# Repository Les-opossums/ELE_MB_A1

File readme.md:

# Motherboard

Electronic board - Motherboard - Main robot - A1

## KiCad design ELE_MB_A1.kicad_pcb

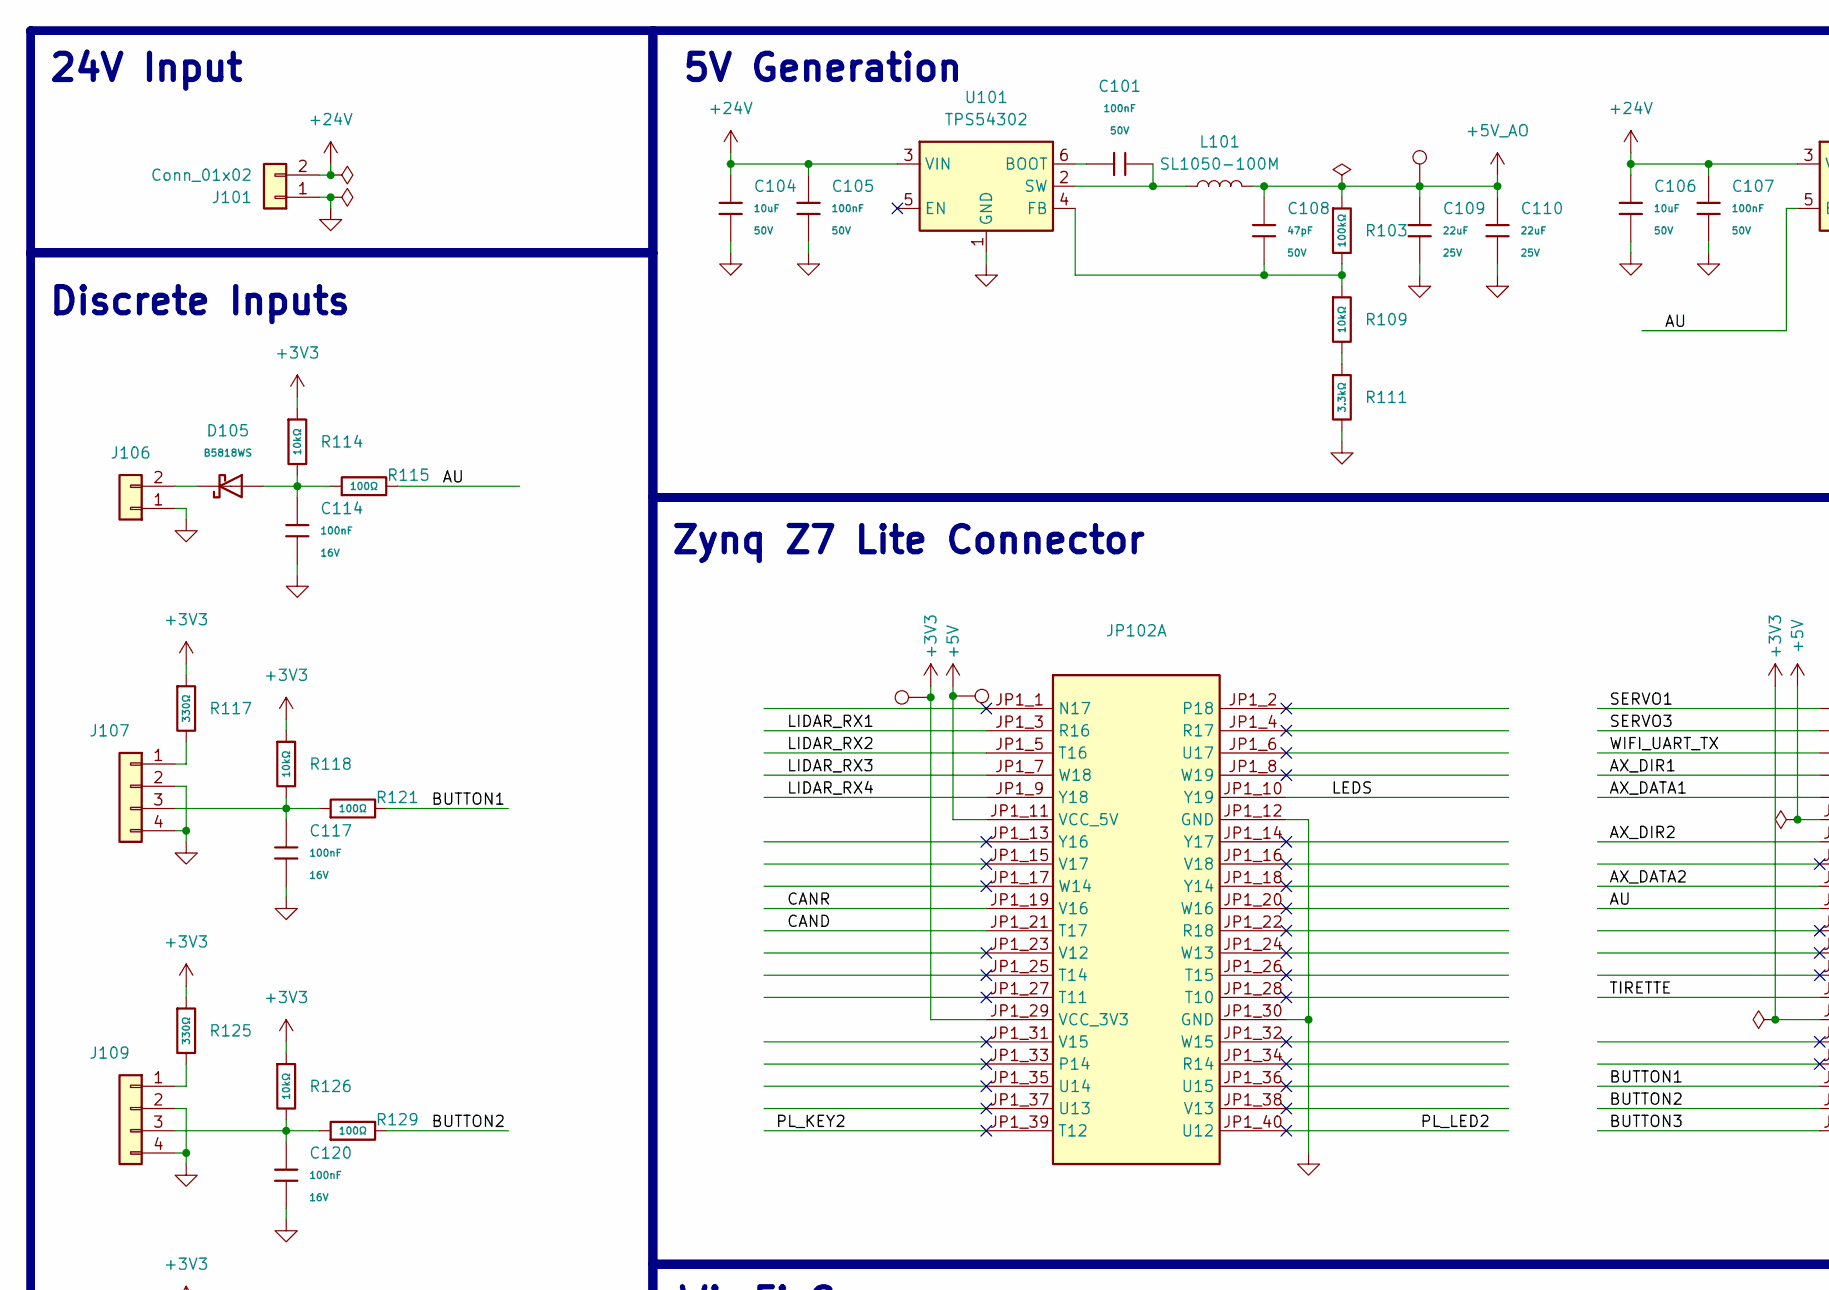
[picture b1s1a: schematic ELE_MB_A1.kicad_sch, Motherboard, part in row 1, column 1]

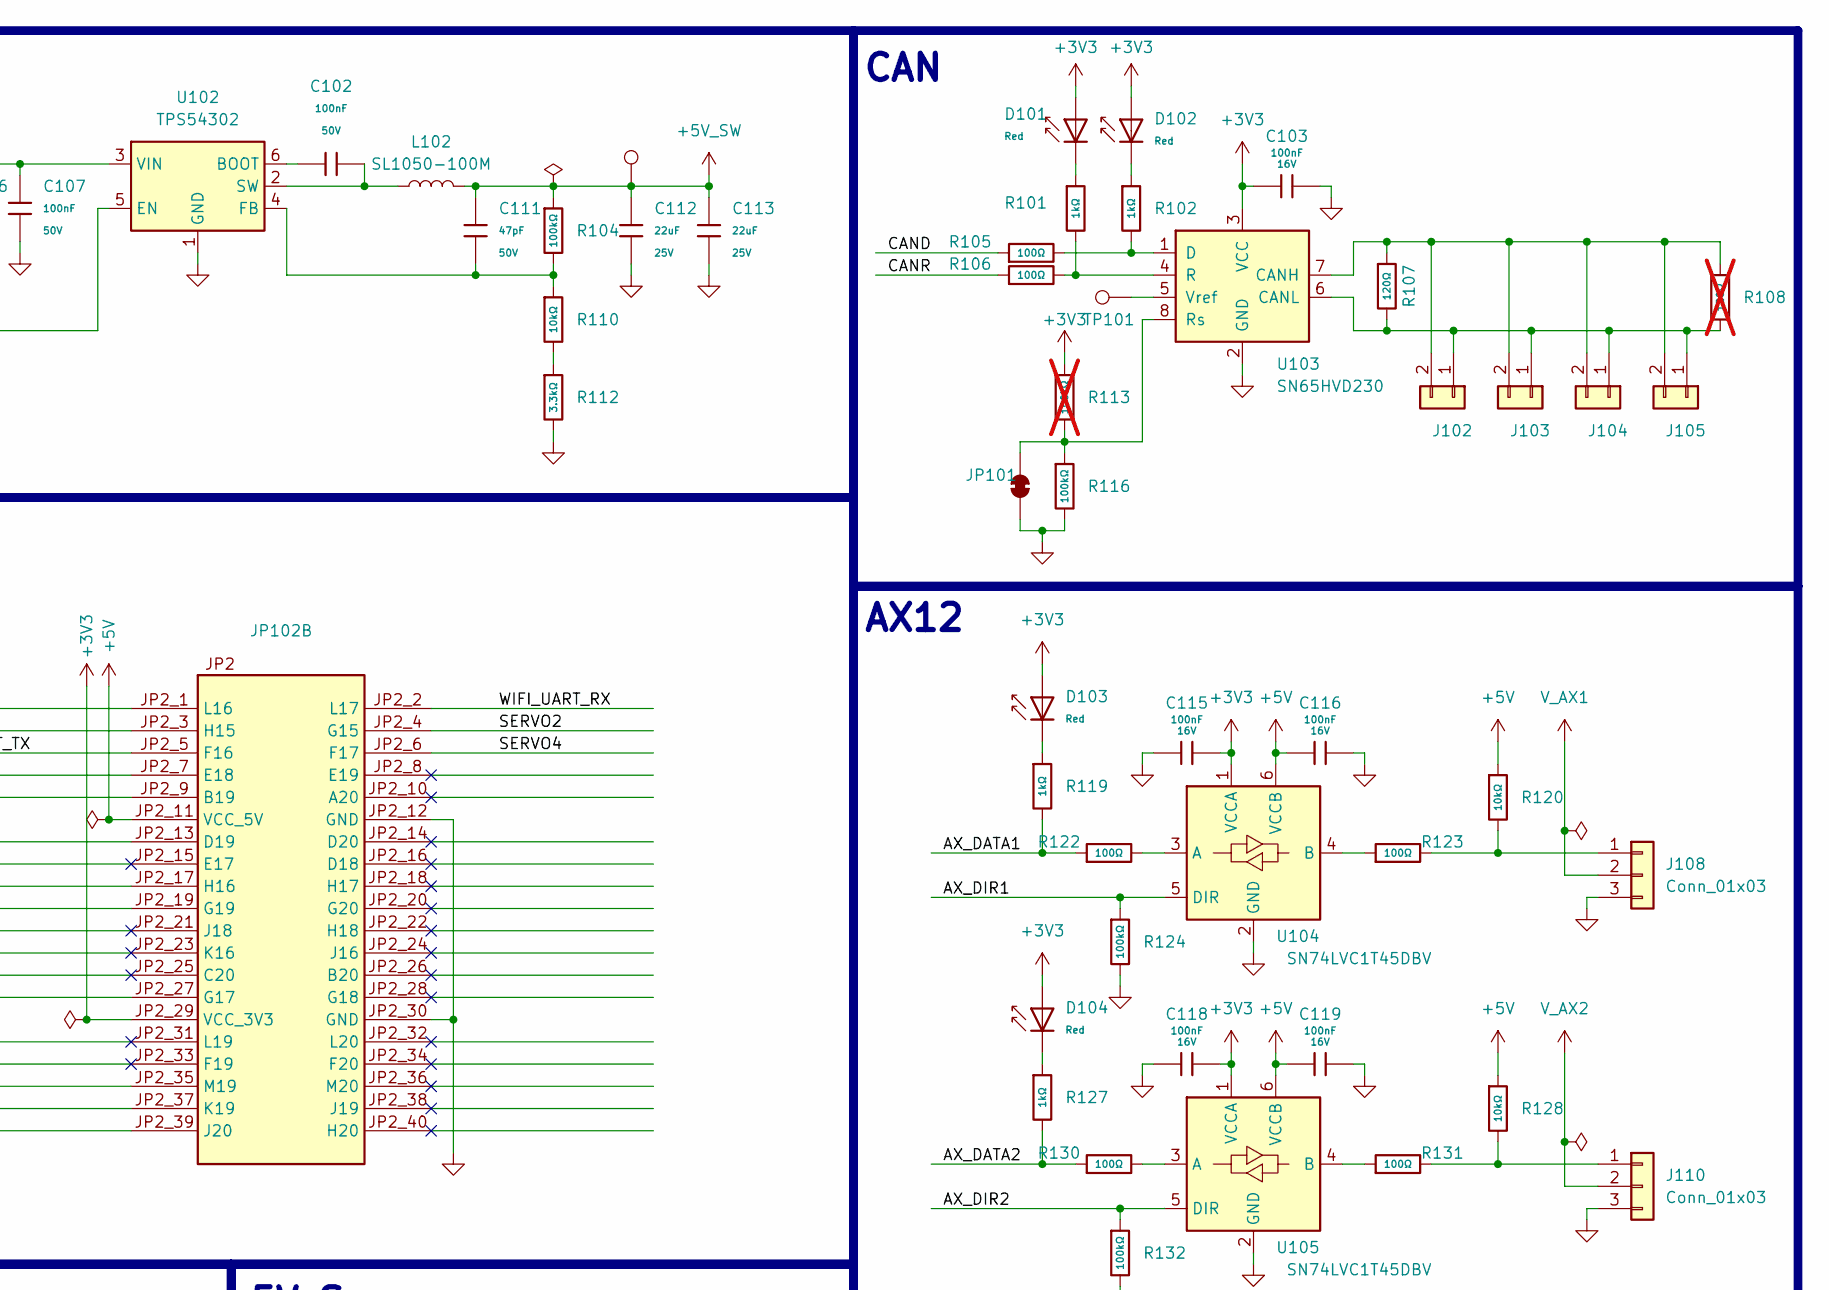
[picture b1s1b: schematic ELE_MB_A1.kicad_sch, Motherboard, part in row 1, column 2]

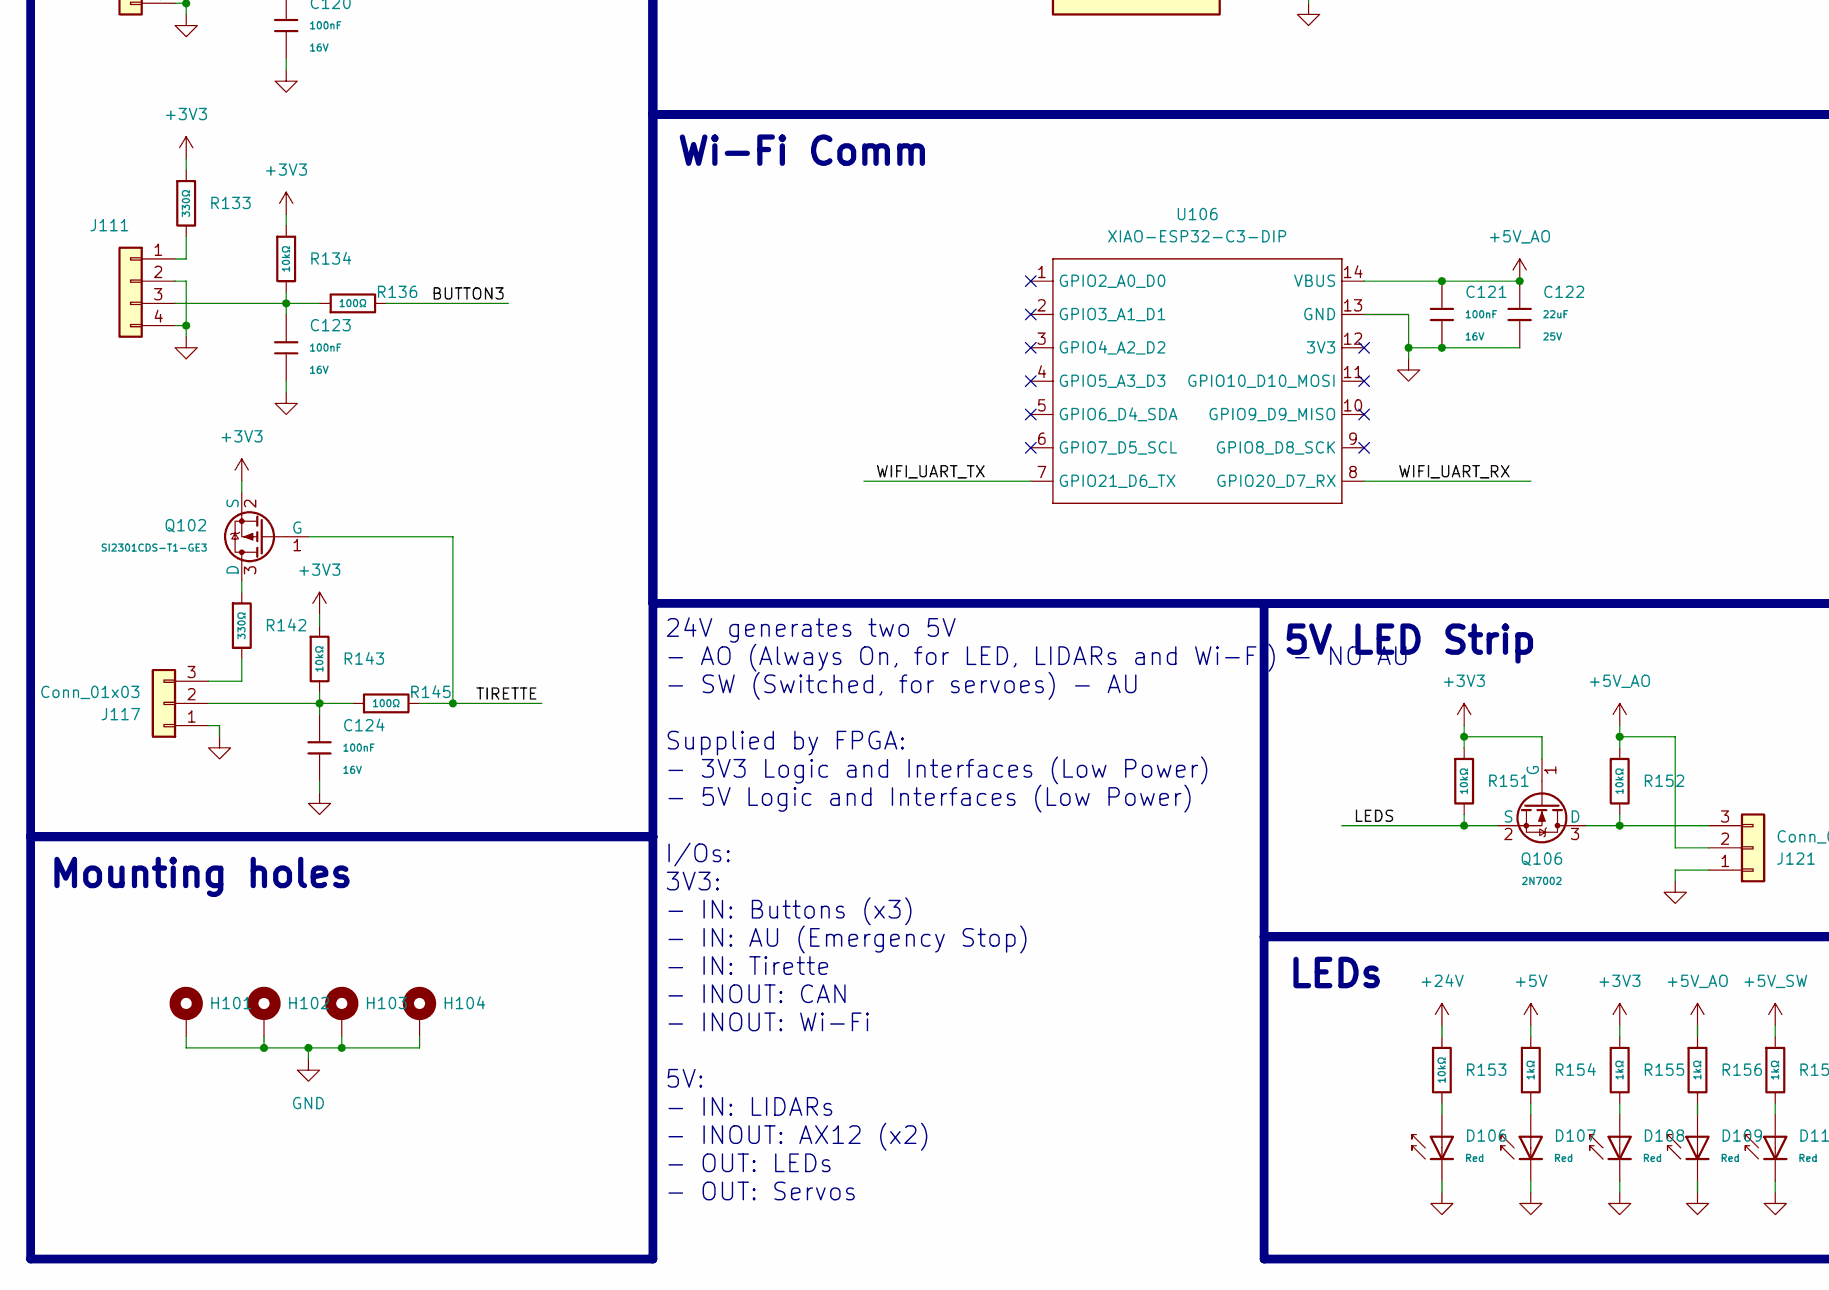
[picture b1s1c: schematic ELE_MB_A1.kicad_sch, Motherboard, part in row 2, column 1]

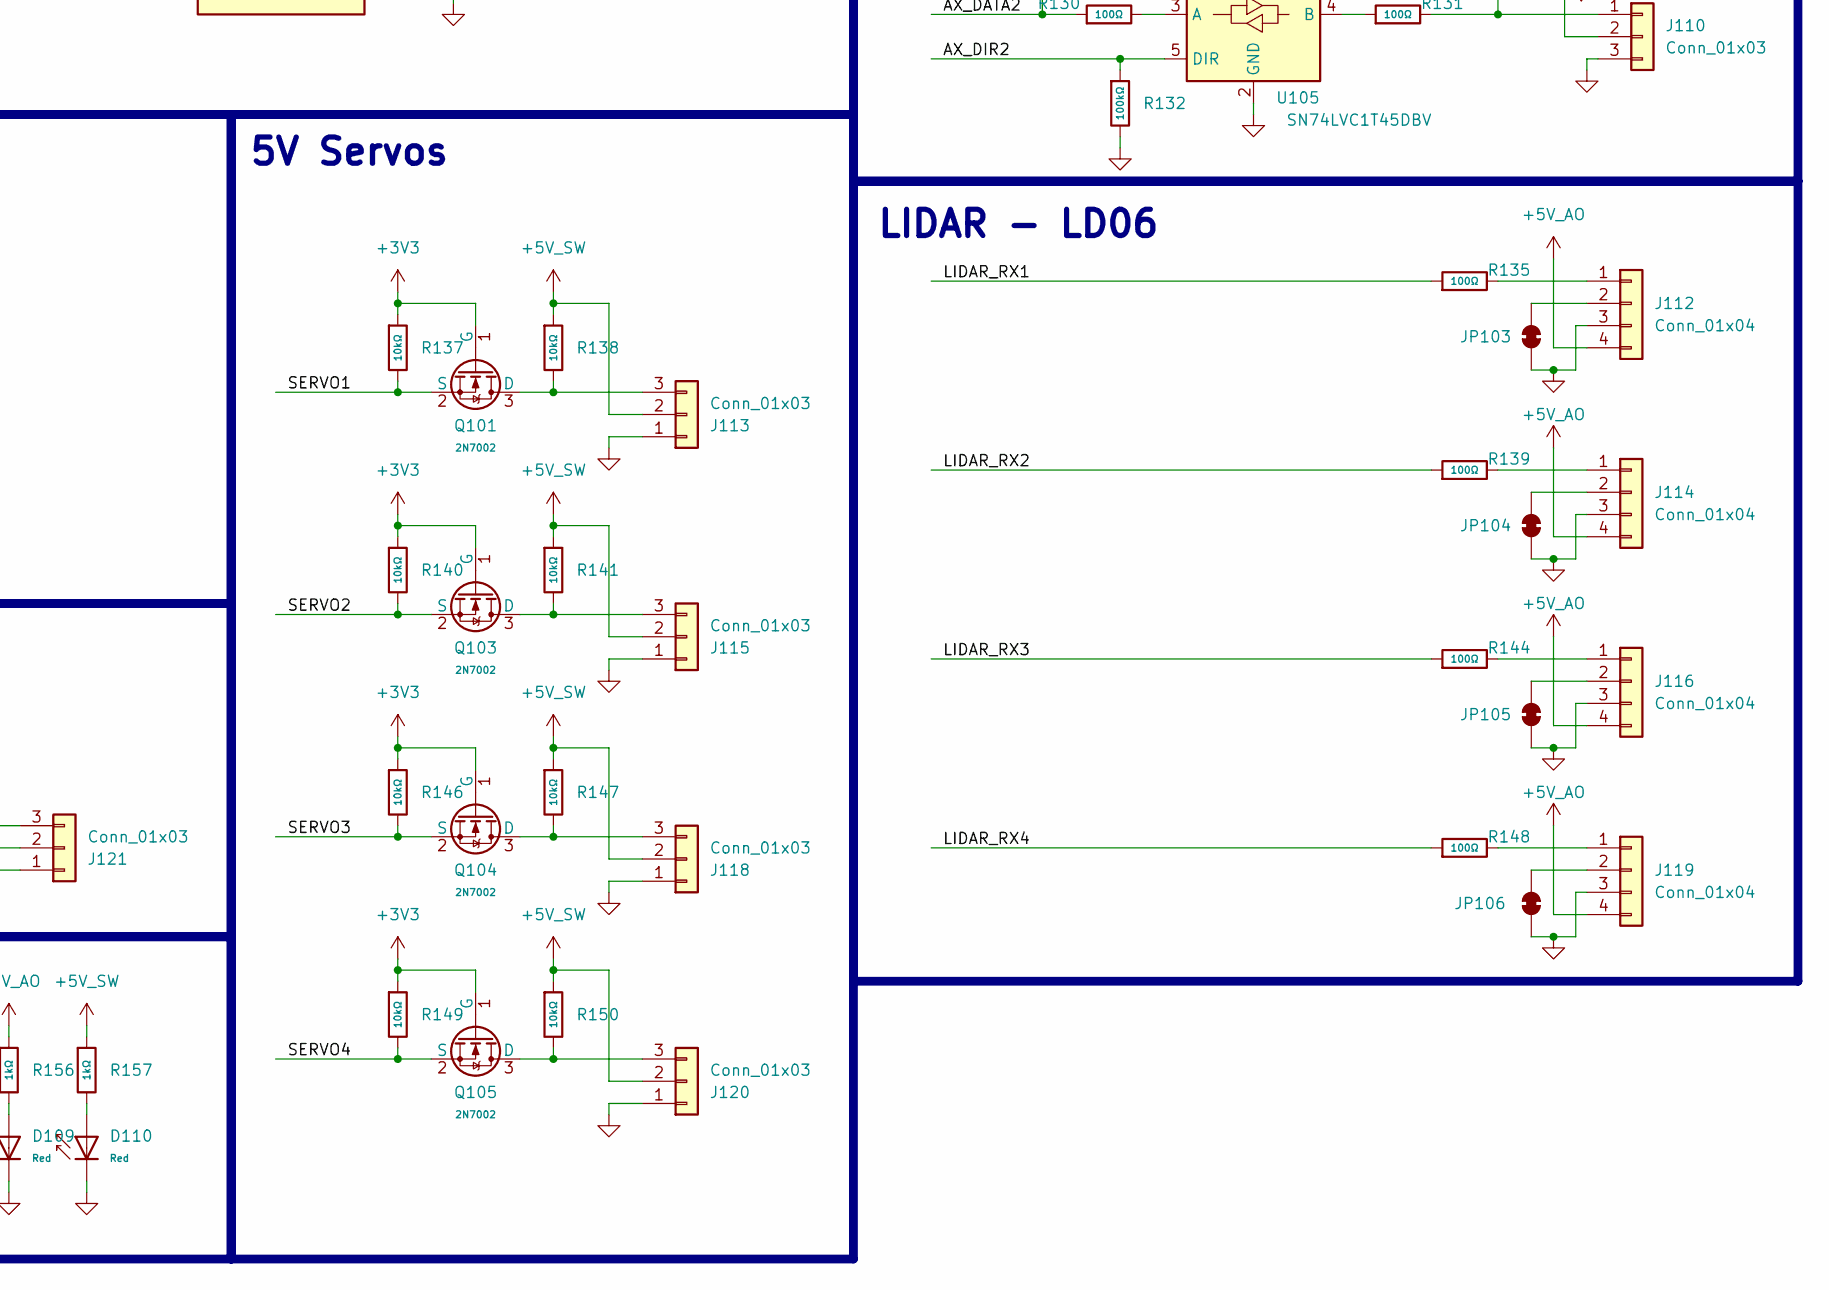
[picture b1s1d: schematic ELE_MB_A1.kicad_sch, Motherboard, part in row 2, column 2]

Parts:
C101, C102, C105, C107: 100nF; C_0603; Voltage Rated 50V; Tolerance ±10%; Part CC0603KRX7R9BB104; LCSC C14663
C103, C114, C115, C116, C117, C118, C119, C120, C121, C123, C124: 100nF; C_0402; Voltage Rated 16V; Tolerance ±10%; Part CL05B104KO5NNNC; LCSC C1525
C104, C106: 10uF; C_1206; Voltage Rated 50V; Tolerance ±10%; Part CL31A106KBHNNNE; LCSC C13585
C108, C111: 47pF; C_0402; Voltage Rated 50V; Tolerance ±5%; Part 0402CG470J500NT; LCSC C1567
C109, C110, C112, C113, C122: 22uF; C_1206; Voltage Rated 25V; Tolerance ±10%; Part CL31A226KAHNNNE; LCSC C12891
D101, D102, D103, D104, D106, D107, D108, D109, D110: Red; D_0603; Part KT-0603R; LCSC C2286
D105: B5818WS; D_SOD-323; Forward Voltage (Vf@If) 550mV@1A; Reverse Voltage (Vr) 30V; Part B5818WS; LCSC C22466361
H101, H102, H103, H104: MountingHole_Pad; MountingHole_3.2mm_M3_DIN965_Pad_TopBottom
J101: Conn_01x02; AMASS_XT30U-F_1x02_P5.0mm_Vertical
J102, J103, J104, J105, J106: Conn_01x02; JST_XH_B2B-XH-A_1x02_P2.50mm_Vertical
J107, J109, J111, J112, J114, J116, J119: Conn_01x04; JST_XH_B4B-XH-A_1x04_P2.50mm_Vertical
J108, J110, J113, J115, J117, J118, J120, J121: Conn_01x03; JST_XH_B3B-XH-A_1x03_P2.50mm_Vertical
JP101, JP103, JP104, JP105, JP106: SolderJumper_2_Bridged; SolderJumper-2_P1.3mm_Bridged_RoundedPad1.0x1.5mm
JP102: Z7-lite
L101, L102: SL1050-100M; L_APV_APH1050
Q101, Q103, Q104, Q105, Q106: 2N7002; Q_SOT-23; Part 2N7002; LCSC C8545
Q102: SI2301CDS-T1-GE3; Q_SOT-23; Part SI2301CDS-T1-GE3; LCSC C10487
R101, R102, R119, R127, R154, R155, R156, R157: 1kΩ; R_0402; Overload Voltage (Max) 50V; Tolerance ±1%; Part 0402WGF1001TCE; LCSC C11702
R103, R104, R116, R124, R132: 100kΩ; R_0402; Overload Voltage (Max) 50V; Tolerance ±1%; Part 0402WGF1003TCE; LCSC C25741
R105, R106, R115, R121, R122, R123, R129, R130, R131, R135, R136, R139, R144, R145, R148: 100Ω; R_0402; Overload Voltage (Max) 50V; Tolerance ±1%; Part 0402WGF1000TCE; LCSC C25076
R107: 120Ω; R_1206; Overload Voltage (Max) 200V; Tolerance ±1%; Part 1206W4F1200T5E; LCSC C17909
R108: 120Ω; R_1206; Overload Voltage (Max) 200V; Tolerance ±1%; Part 1206W4F1200T5E; LCSC C17909; not fitted
R109, R110, R114, R118, R120, R126, R128, R134, R137, R138, R140, R141, R143, R146, R147, R149, R150, R151, R152, R153: 10kΩ; R_0402; Overload Voltage (Max) 50V; Tolerance ±1%; Part 0402WGF1002TCE; LCSC C25744
R111, R112: 3.3kΩ; R_0402; Overload Voltage (Max) 50V; Tolerance ±1%; Part 0402WGF3301TCE; LCSC C25890
R113: 100kΩ; R_0402; Overload Voltage (Max) 50V; Tolerance ±1%; Part 0402WGF1003TCE; LCSC C25741; not fitted
R117, R125, R133, R142: 330Ω; R_0402; Overload Voltage (Max) 50V; Tolerance ±1%; Part 0402WGF3300TCE; LCSC C25104
TP101: TestPoint; TestPoint_Pad_D1.0mm
TP102, TP103, TP104, TP105: TestPoint; TestPoint_THTPad_D1.0mm_Drill0.5mm
U101, U102: TPS54302; SOT-23-6
U103: SN65HVD230; SOIC-8_3.9x4.9mm_P1.27mm
U104, U105: SN74LVC1T45DBV; SOT-23-6
U106: XIAO-ESP32-C3-DIP

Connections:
+3V3: C103.1, C115.1, C118.1, D101.2, D102.2, D103.2, D104.2, JP102.JP1_29 (VCC_3V3), JP102.JP2_29 (VCC_3V3), Q101.1 (G), Q102.2 (S), Q103.1 (G), Q104.1 (G), Q105.1 (G), Q106.1 (G), R113.1, R114.1, R117.1, R118.1, R125.1, R126.1, R133.1, R134.1, R137.1, R140.1, R143.1, R146.1, R149.1, R151.1, R155.1, TP105.1, U103.3 (VCC), U104.1 (VCCA), U105.1 (VCCA)
+5V: C116.1, C119.1, JP102.JP1_11 (VCC_5V), JP102.JP2_11 (VCC_5V), R120.1, R128.1, R154.1, TP104.1, U104.6 (VCCB), U105.6 (VCCB)
+5V_AO: C108.1, C109.1, C110.1, C121.1, C122.1, J112.4, J114.4, J116.4, J119.4, J121.2, L101.2, R103.1, R152.1, R156.1, TP102.1, U106.14 (VBUS)
+5V_SW: C111.1, C112.1, C113.1, J113.2, J115.2, J118.2, J120.2, L102.2, R104.1, R138.1, R141.1, R147.1, R150.1, R157.1, TP103.1
+24V: C104.1, C105.2, C106.1, C107.2, J101.2, R153.1, U101.3 (VIN), U102.3 (VIN)
/AU: JP102.JP2_19 (G19), R115.2, U102.5 (EN)
/AX_DATA1: JP102.JP2_9 (B19), R119.2, R122.1
/AX_DATA2: JP102.JP2_17 (H16), R127.2, R130.1
/AX_DIR1: JP102.JP2_7 (E18), R124.1, U104.5 (DIR)
/AX_DIR2: JP102.JP2_13 (D19), R132.1, U105.5 (DIR)
/BUTTON1: JP102.JP2_35 (M19), R121.2
/BUTTON2: JP102.JP2_37 (K19), R129.2
/BUTTON3: JP102.JP2_39 (J20), R136.2
/CAND: JP102.JP1_21 (T17), R105.1
/CANR: JP102.JP1_19 (V16), R106.1
/LEDS: JP102.JP1_10 (Y19), Q106.2 (S), R151.2
/LIDAR_RX1: JP102.JP1_3 (R16), R135.1
/LIDAR_RX2: JP102.JP1_5 (T16), R139.1
/LIDAR_RX3: JP102.JP1_7 (W18), R144.1
/LIDAR_RX4: JP102.JP1_9 (Y18), R148.1
/PL_KEY2: JP102.JP1_39 (T12)
/PL_LED2: JP102.JP1_40 (U12)
/SERVO1: JP102.JP2_1 (L16), Q101.2 (S), R137.2
/SERVO2: JP102.JP2_4 (G15), Q103.2 (S), R140.2
/SERVO3: JP102.JP2_3 (H15), Q104.2 (S), R146.2
/SERVO4: JP102.JP2_6 (F17), Q105.2 (S), R149.2
/TIRETTE: JP102.JP2_27 (G17), Q102.1 (G), R145.2
/WIFI_UART_RX: JP102.JP2_2 (L17), U106.8 (GPIO20_D7_RX)
/WIFI_UART_TX: JP102.JP2_5 (F16), U106.7 (GPIO21_D6_TX)
GND: C103.2, C104.2, C105.1, C106.2, C107.1, C109.2, C110.2, C112.2, C113.2, C114.2, C115.2, C116.2, C117.2, C118.2, C119.2, C120.2, C121.2, C122.2, C123.2, C124.2, D106.1, D107.1, D108.1, D109.1, D110.1, H101.1, H102.1, H103.1, H104.1, J101.1, J106.1, J107.2, J107.4, J108.3, J109.2, J109.4, J110.3, J111.2, J111.4, J112.3, J113.1, J114.3, J115.1, J116.3, J117.1, J118.1, J119.3, J120.1, J121.1, JP101.1 (A), JP102.JP1_12 (GND), JP102.JP1_30 (GND), JP102.JP2_12 (GND), JP102.JP2_30 (GND), JP103.1 (A), JP104.1 (A), JP105.1 (A), JP106.1 (A), R111.2, R112.2, R116.2, R124.2, R132.2, U101.1 (GND), U102.1 (GND), U103.2 (GND), U104.2 (GND), U105.2 (GND), U106.13 (GND)
unnamed: C114.1, D105.2, R114.2, R115.1
unnamed: D101.1, R101.1
unnamed: D102.1, R102.1
unnamed: D103.1, R119.1
unnamed: D104.1, R127.1
unnamed: D106.2, R153.2
unnamed: D107.2, R154.2
unnamed: D108.2, R155.2
unnamed: D109.2, R156.2
unnamed: D110.2, R157.2
unnamed: J102.1, J103.1, J104.1, J105.1, R107.2, R108.2, U103.6 (CANL)
unnamed: J102.2, J103.2, J104.2, J105.2, R107.1, R108.1, U103.7 (CANH)
unnamed: D105.1, J106.2
unnamed: J107.1, R117.2
unnamed: C117.1, J107.3, R118.2, R121.1
unnamed: J108.1, R120.2, R123.2
unnamed: J109.1, R125.2
unnamed: C120.1, J109.3, R126.2, R129.1
unnamed: J110.1, R128.2, R131.2
unnamed: J111.1, R133.2
unnamed: C123.1, J111.3, R134.2, R136.1
unnamed: J112.1, R135.2
unnamed: J112.2, JP103.2 (B)
unnamed: J113.3, Q101.3 (D), R138.2
unnamed: J114.1, R139.2
unnamed: J114.2, JP104.2 (B)
unnamed: J115.3, Q103.3 (D), R141.2
unnamed: J116.1, R144.2
unnamed: J116.2, JP105.2 (B)
unnamed: C124.1, J117.2, R143.2, R145.1
unnamed: J117.3, R142.2
unnamed: J118.3, Q104.3 (D), R147.2
unnamed: J119.1, R148.2
unnamed: J119.2, JP106.2 (B)
unnamed: J120.3, Q105.3 (D), R150.2
unnamed: J121.3, Q106.3 (D), R152.2
unnamed: JP101.2 (B), R113.2, R116.1, U103.8 (Rs)
unnamed: Q102.3 (D), R142.1
unnamed: R109.2, R111.1
unnamed: R110.2, R112.1
unnamed: C101.1, U101.6 (BOOT)
unnamed: C108.2, R103.2, R109.1, U101.4 (FB)
unnamed: C101.2, L101.1, U101.2 (SW)
unnamed: C102.1, U102.6 (BOOT)
unnamed: C111.2, R104.2, R110.1, U102.4 (FB)
unnamed: C102.2, L102.1, U102.2 (SW)
unnamed: R102.2, R105.2, U103.1 (D)
unnamed: R101.2, R106.2, U103.4 (R)
unnamed: TP101.1, U103.5 (Vref)
unnamed: R122.2, U104.3 (A)
unnamed: R123.1, U104.4 (B)
unnamed: R130.2, U105.3 (A)
unnamed: R131.1, U105.4 (B)
V_AX1: J108.2
V_AX2: J110.2

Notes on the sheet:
LEDs
5V LED Strip
Wi-Fi Comm
AX12
5V Generation
Zynq Z7 Lite Connector
24V Input
LIDAR - LD06
Mounting holes
CAN
5V Servos
Discrete Inputs
24V generates two 5V - AO (Always On, for LED, LIDARs and Wi-Fi) - NO AU - SW (Switched, for servoes) - AU Supplied by FPGA: - 3V3 Logic and Interfaces (Low Power) - 5V Logic and Interfaces (Low Power) I/Os: 3V3: - IN: Buttons (x3) - IN: AU (Emergency Stop) - IN: Tirette - INOUT: CAN - INOUT: Wi-Fi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

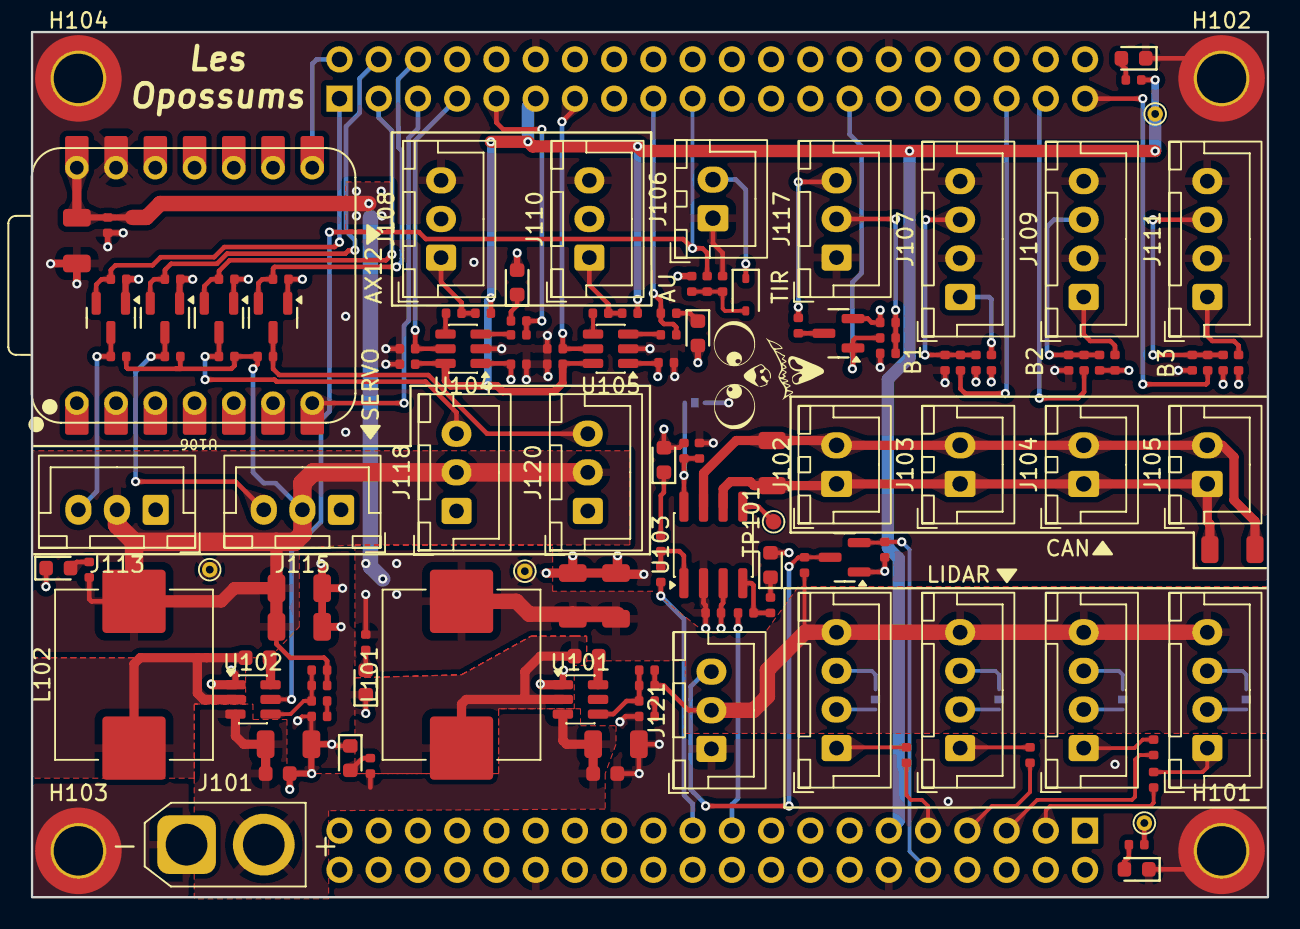
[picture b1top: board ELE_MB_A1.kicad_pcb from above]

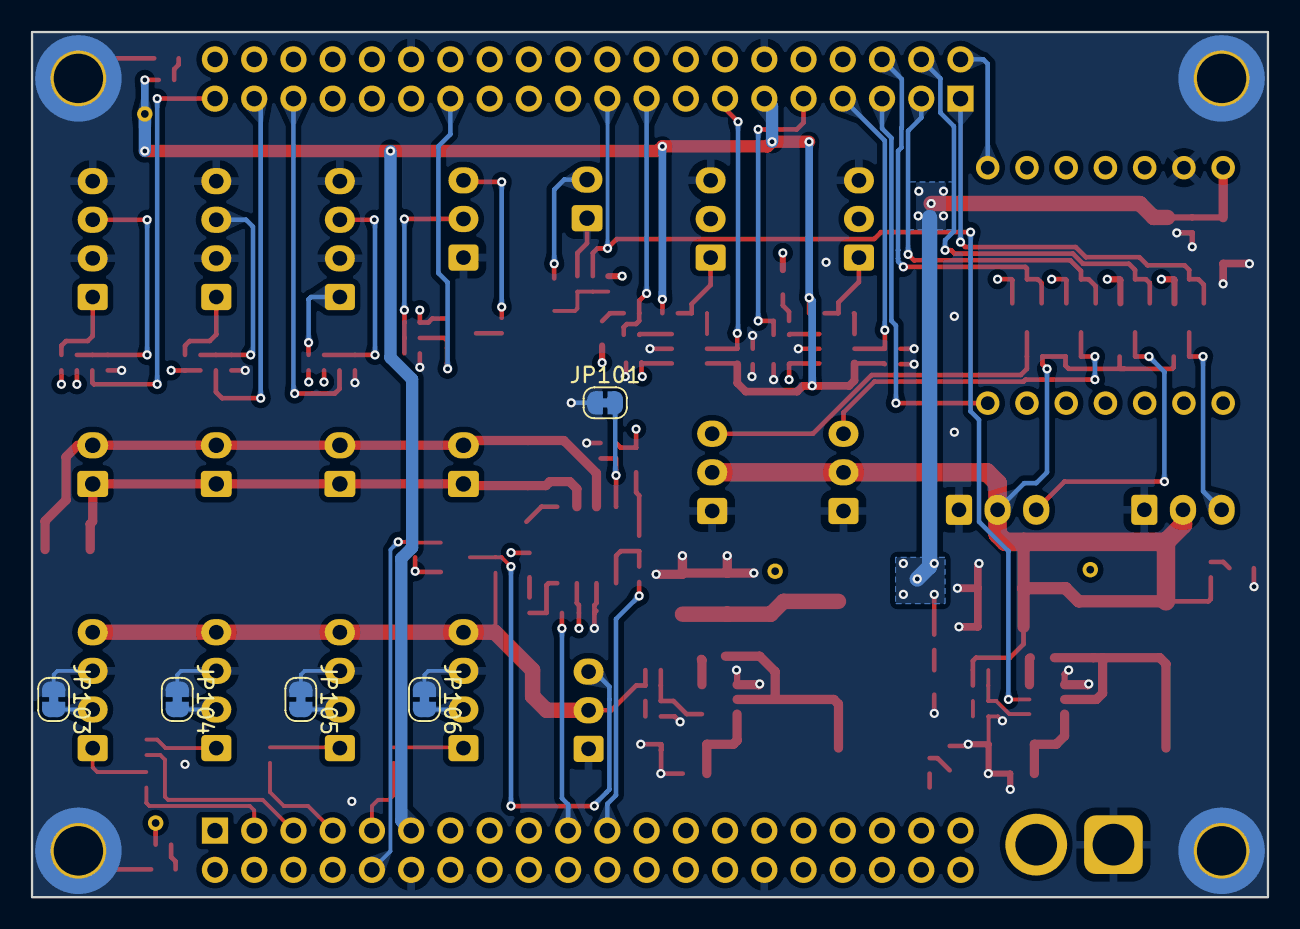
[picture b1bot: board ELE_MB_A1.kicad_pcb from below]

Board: 4 copper layers, 80.0 x 56.0 mm, 141 parts (5 on the bottom side), 81 nets.

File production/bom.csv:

Designator,Footprint,Quantity,Value,LCSC Part #
"C101, C102, C105, C107",C_0603,4,100nF,C14663
"C103, C114, C115, C116, C117, C118, C119, C120, C121, C123, C124",C_0402,11,100nF,C1525
"C104, C106",C_1206,2,10uF,C13585
"C108, C111",C_0402,2,47pF,C1567
"C109, C110, C112, C113, C122",C_1206,5,22uF,C12891
"D101, D102, D103, D104, D106, D107, D108, D109, D110",D_0603,9,Red,C2286
D105,D_SOD-323,1,B5818WS,C22466361
J101,AMASS_XT30U-F_1x02_P5.0mm_Vertical,1,Conn_01x02,
"J102, J103, J104, J105, J106",JST_XH_B2B-XH-A_1x02_P2.50mm_Vertical,5,Conn_01x02,
"J107, J109, J111, J112, J114, J116, J119",JST_XH_B4B-XH-A_1x04_P2.50mm_Vertical,7,Conn_01x04,
"J108, J110, J113, J115, J117, J118, J120, J121",JST_XH_B3B-XH-A_1x03_P2.50mm_Vertical,8,Conn_01x03,
JP102,Z7-lite,1,~,
"L101, L102",L_APV_APH1050,2,SL1050-100M,
"Q101, Q103, Q104, Q105, Q106",Q_SOT-23,5,2N7002,C8545
Q102,Q_SOT-23,1,SI2301CDS-T1-GE3,C10487
"R101, R102, R119, R127, R154, R155, R156, R157",R_0402,8,1kΩ,C11702
"R103, R104, R116, R124, R132",R_0402,5,100kΩ,C25741
"R105, R106, R115, R121, R122, R123, R129, R130, R131, R135, R136, R139, R144, R145, R148",R_0402,15,100Ω,C25076
R107,R_1206,1,120Ω,C17909
"R109, R110, R114, R118, R120, R126, R128, R134, R137, R138, R140, R141, R143, R146, R147, R149, R150, R151, R152, R153",R_0402,20,10kΩ,C25744
"R111, R112",R_0402,2,3.3kΩ,C25890
"R117, R125, R133, R142",R_0402,4,330Ω,C25104
TP101,TestPoint_Pad_D1.0mm,1,TestPoint,
"TP102, TP103, TP104, TP105",TestPoint_THTPad_D1.0mm_Drill0.5mm,4,TestPoint,
"U101, U102",SOT-23-6,2,TPS54302,
U103,SOIC-8_3.9x4.9mm_P1.27mm,1,SN65HVD230,
"U104, U105",SOT-23-6,2,SN74LVC1T45DBV,
U106,XIAO-ESP32-C3-DIP,1,XIAO-ESP32-C3-DIP,

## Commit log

2026-03-15 Finished board
2026-03-15 Vraiment finished
